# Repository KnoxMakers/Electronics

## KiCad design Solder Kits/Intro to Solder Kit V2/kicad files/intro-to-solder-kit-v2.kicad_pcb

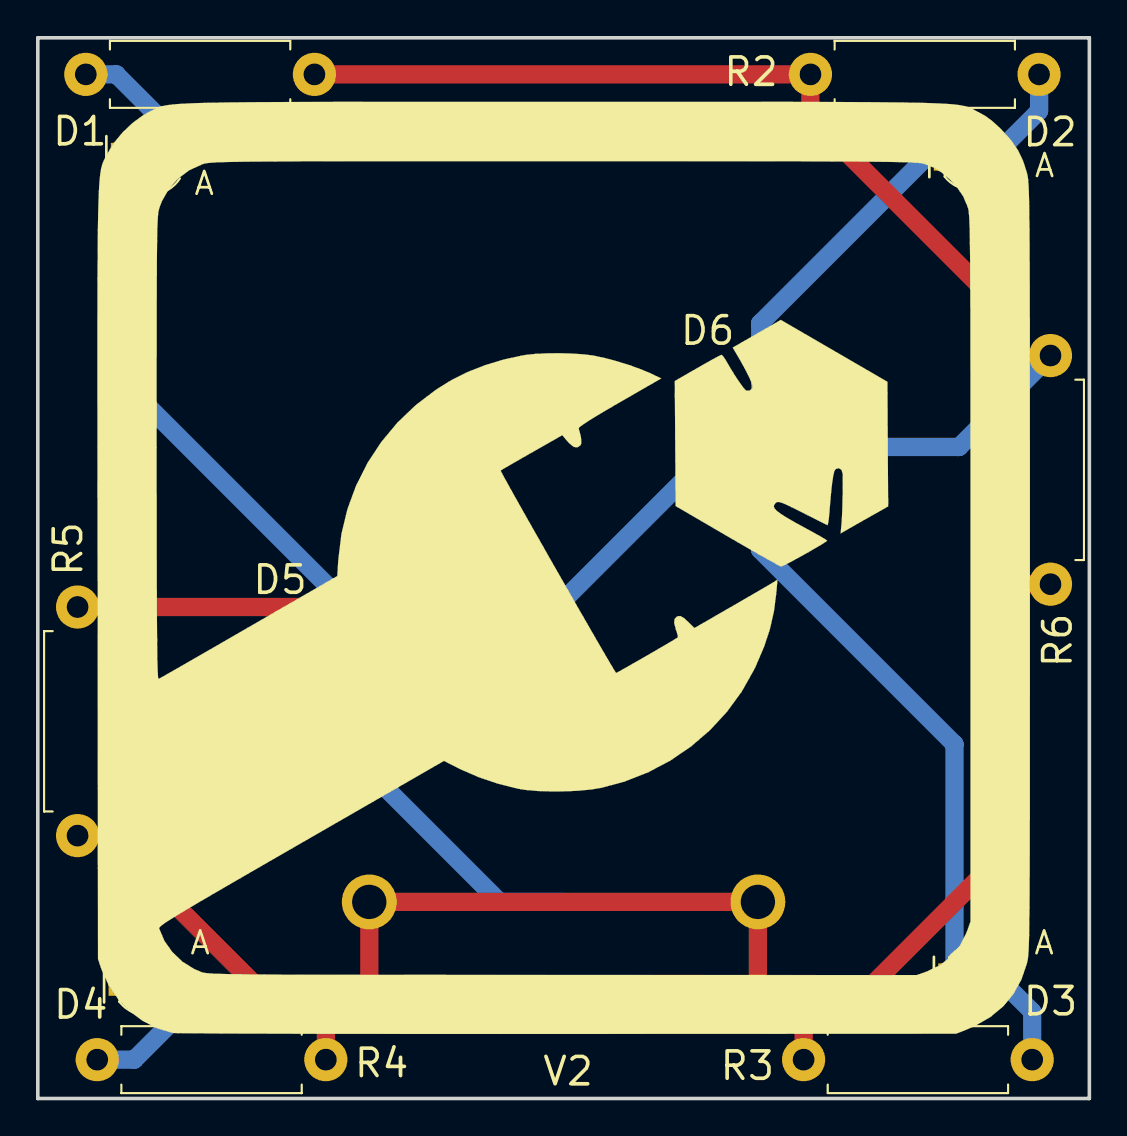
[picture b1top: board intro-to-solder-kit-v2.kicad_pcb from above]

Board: 2 copper layers, 58.4 x 58.9 mm, 14 parts (1 on the bottom side), 8 nets.

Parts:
BT1: CR2032; Keystone-3035-CR2032-Coin
D1, D2, D3, D4, D5, D6: LED; LED_D3.0mm
KM_LOGO1: KM LOGO FOOTPRINT; km-logo
R1, R2, R3, R4, R5, R6: 51; R_Axial_DIN0411_L9.9mm_D3.6mm_P12.70mm_Horizontal

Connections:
GND: BT1.2, D1.1, D2.1, D3.1, D4.1, D5.1, D6.1
unnamed: BT1.1, R1.1, R2.1, R3.1, R4.1, R5.1, R6.1
unnamed: D1.2, R1.2
unnamed: D2.2, R2.2
unnamed: D3.2, R3.2
unnamed: D4.2, R4.2
unnamed: D5.2, R5.2
unnamed: D6.2, R6.2
